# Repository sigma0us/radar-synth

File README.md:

# radar-synth
Dual PLL radar transmitter, design for prototyping

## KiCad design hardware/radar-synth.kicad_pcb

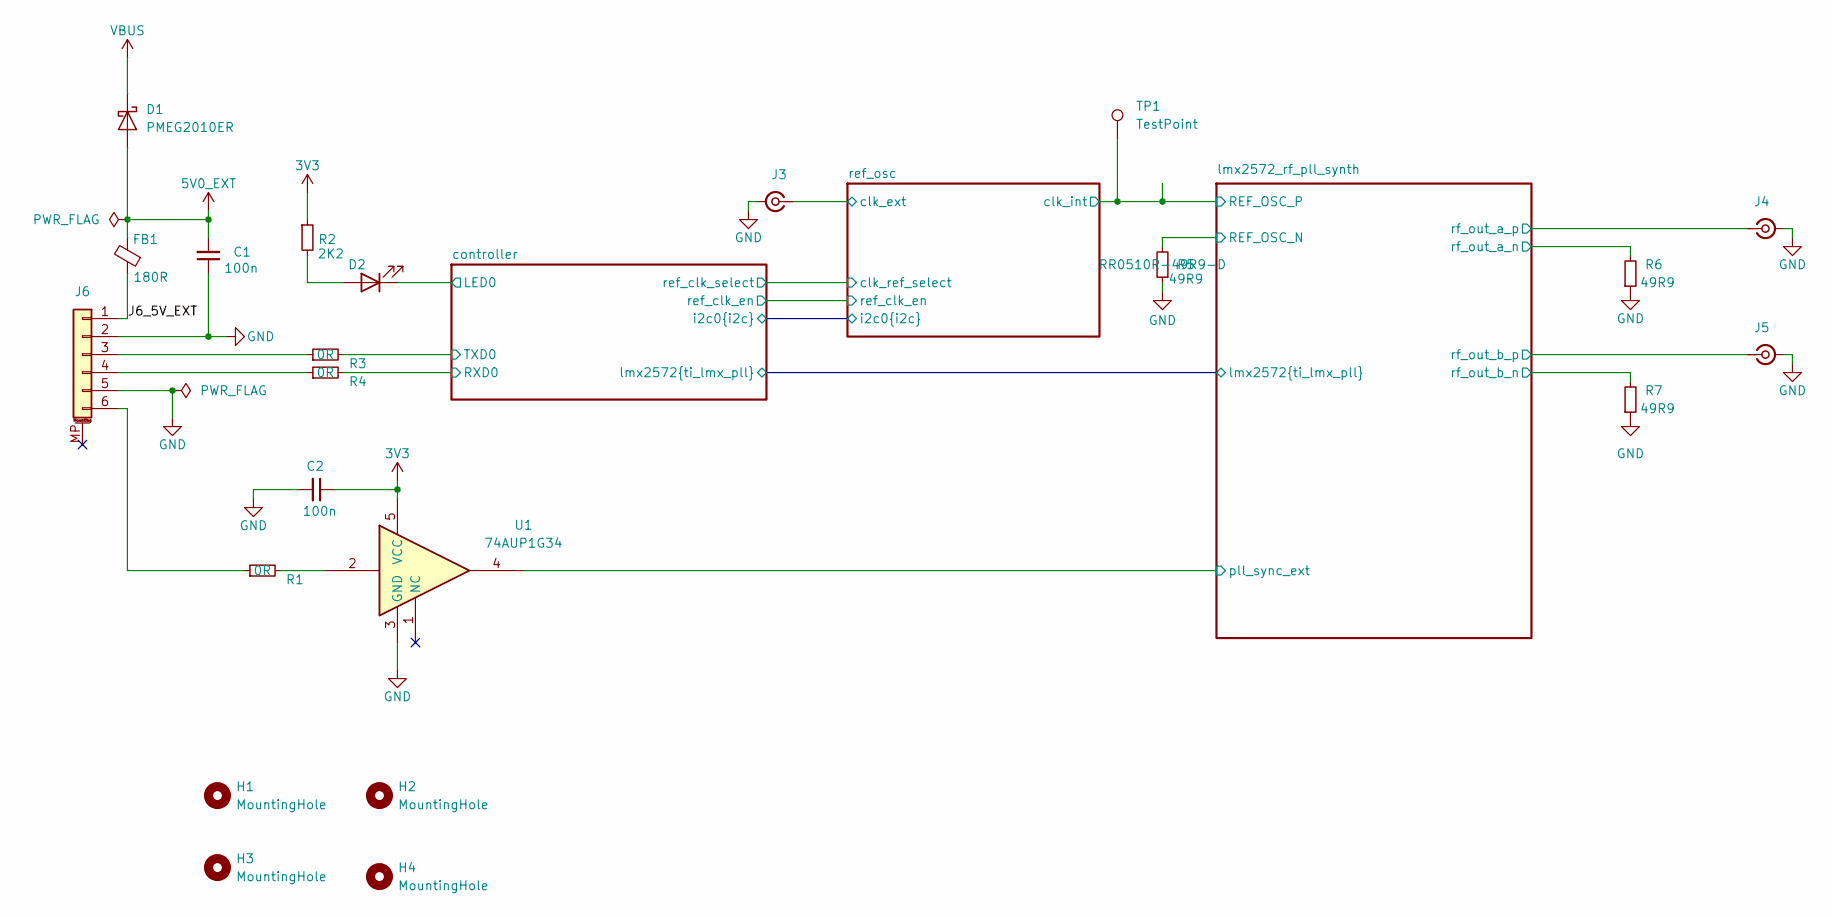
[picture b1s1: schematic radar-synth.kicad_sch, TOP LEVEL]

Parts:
C1, C2: 100n; C_0402_1005Metric; Voltage 25V; Tolerance 10%; MPN CL05B104KA5NNNC
D1: PMEG2010ER; Nexperia_CFP3_SOD-123W; MPN PMEG2010ER,115
D2: LED; LED_0603_1608Metric; MPN 150060SS75000
FB1: 180R; L_0402_1005Metric; MPN BLM15PX181SZ1D
H1, H2, H3, H4: MountingHole; MountingHole_2.7mm_M2.5
J3, J4, J5: Conn_Coaxial_Small; SMA_Samtec_SMA-J-P-H-ST-EM1_EdgeMount; MPN SMA-J-P-H-ST-EM1
J6: Conn_01x06_MountingPin; JST_GH_SM06B-GHS-TB_1x06-1MP_P1.25mm_Horizontal; MPN SM06B-GHS-TB
R1, R3, R4: 0R; R_0402_1005Metric; MPN ERJ-2GE0R00X
R2: 2K2; R_0402_1005Metric; MPN ERA-2AED222X
R5: 49R9; R_0402_1005Metric; Tolerance 5%; MPN RR0510R-49R9-D
R6, R7: 49R9; R_0402_1005Metric; MPN RR0510R-49R9-D
TP1: TestPoint; TestPoint_THTPad_1.0x1.0mm_Drill0.5mm
U1: 74AUP1G34; SOT-353_SC-70-5; MPN 74AUP1G34SE-7

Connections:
3V3: C2.1, R2.1, U1.5 (VCC); also elsewhere on the board
5V0_EXT: C1.2, D1.2 (A), FB1.2
/J6_5V_EXT: FB1.1, J6.1
/controller/LED0: D2.1 (K); also elsewhere on the board
/controller/RXD0: R4.2; also elsewhere on the board
/controller/TXD0: R3.2; also elsewhere on the board
/lmx2572_rf_pll_synth/REF_OSC_N: R5.2; also elsewhere on the board
/lmx2572_rf_pll_synth/REF_OSC_P: TP1.1; also elsewhere on the board
/lmx2572_rf_pll_synth/pll_sync_ext: U1.4; also elsewhere on the board
/lmx2572_rf_pll_synth/rf_out_a_n: R6.2; also elsewhere on the board
/lmx2572_rf_pll_synth/rf_out_a_p: J4.1 (In); also elsewhere on the board
/lmx2572_rf_pll_synth/rf_out_b_n: R7.2; also elsewhere on the board
/lmx2572_rf_pll_synth/rf_out_b_p: J5.1 (In); also elsewhere on the board
/ref_osc/clk_ext: J3.1 (In); also elsewhere on the board
GND: C1.1, C2.2, J3.2 (Ext), J4.2 (Ext), J5.2 (Ext), J6.2, J6.5, R5.1, R6.1, R7.1, U1.3 (GND); also elsewhere on the board
unnamed: D2.2 (A), R2.2
unnamed: J6.3, R3.1
unnamed: J6.4, R4.1
unnamed: J6.6, R1.1
unnamed: R1.2, U1.2
VBUS: D1.1 (K); also elsewhere on the board

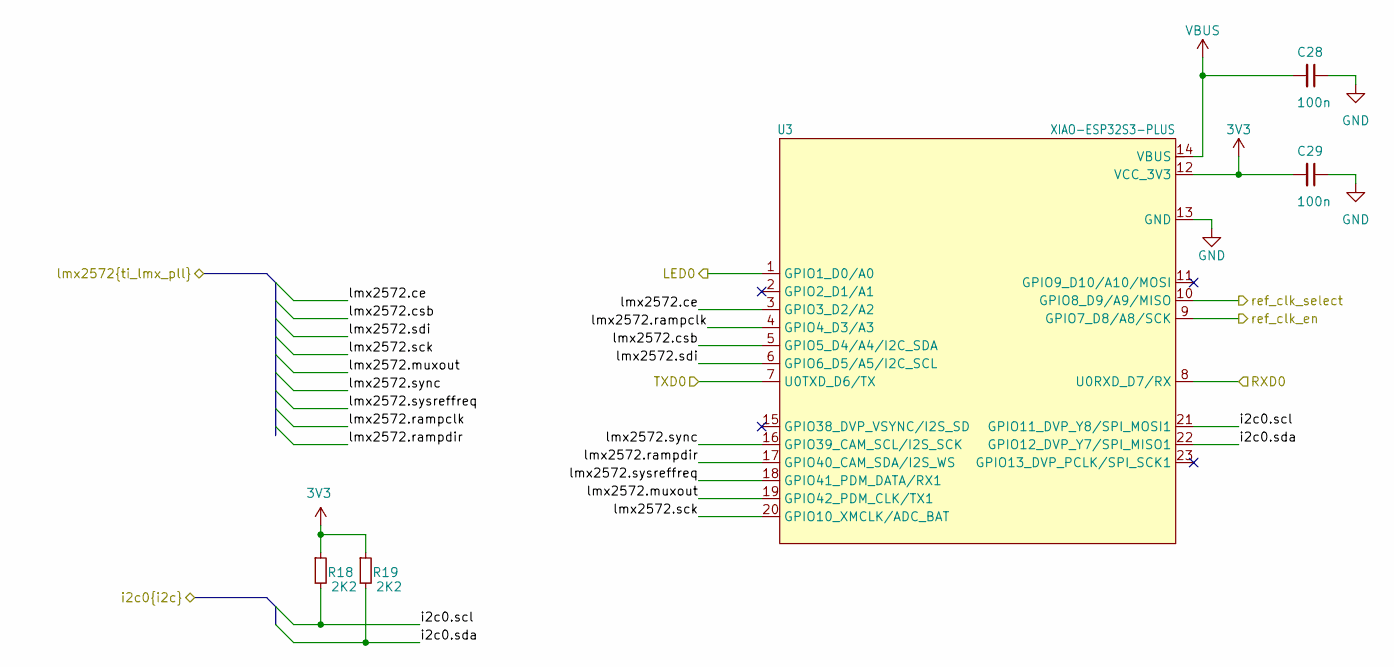
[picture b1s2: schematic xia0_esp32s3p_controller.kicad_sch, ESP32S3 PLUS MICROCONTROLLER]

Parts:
C28, C29: 100n; C_0402_1005Metric; Voltage 25V; Tolerance 10%; MPN CL05B104KA5NNNC
R18, R19: 2K2; R_0402_1005Metric; MPN ERA-2AED222X
U3: XIAO-ESP32S3-PLUS; XIAO-ESP32S3P-SMD-2.54-21X17.8MM; MPN 113991114

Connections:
3V3: C29.2, R18.1, R19.1, U3.12 (VCC_3V3); also elsewhere on the board
/controller/LED0: U3.1 (GPIO1_D0/A0); also elsewhere on the board
/controller/RXD0: U3.8 (U0RXD_D7/RX); also elsewhere on the board
/controller/TXD0: U3.7 (U0TXD_D6/TX); also elsewhere on the board
/controller/i2c0.scl: R18.2, U3.21 (GPIO11_DVP_Y8/SPI_MOSI1); also elsewhere on the board
/controller/i2c0.sda: R19.2, U3.22 (GPIO12_DVP_Y7/SPI_MISO1); also elsewhere on the board
/controller/lmx2572.ce: U3.3 (GPIO3_D2/A2); also elsewhere on the board
/controller/lmx2572.csb: U3.5 (GPIO5_D4/A4/I2C_SDA); also elsewhere on the board
/controller/lmx2572.muxout: U3.19 (GPIO42_PDM_CLK/TX1); also elsewhere on the board
/controller/lmx2572.rampclk: U3.4 (GPIO4_D3/A3); also elsewhere on the board
/controller/lmx2572.rampdir: U3.17 (GPIO40_CAM_SDA/I2S_WS); also elsewhere on the board
/controller/lmx2572.sck: U3.20 (GPIO10_XMCLK/ADC_BAT); also elsewhere on the board
/controller/lmx2572.sdi: U3.6 (GPIO6_D5/A5/I2C_SCL); also elsewhere on the board
/controller/lmx2572.sync: U3.16 (GPIO39_CAM_SCL/I2S_SCK); also elsewhere on the board
/controller/lmx2572.sysreffreq: U3.18 (GPIO41_PDM_DATA/RX1); also elsewhere on the board
/controller/ref_clk_en: U3.9 (GPIO7_D8/A8/SCK); also elsewhere on the board
/controller/ref_clk_select: U3.10 (GPIO8_D9/A9/MISO); also elsewhere on the board
GND: C28.1, C29.1, U3.13 (GND); also elsewhere on the board
VBUS: C28.2, U3.14 (VBUS); also elsewhere on the board

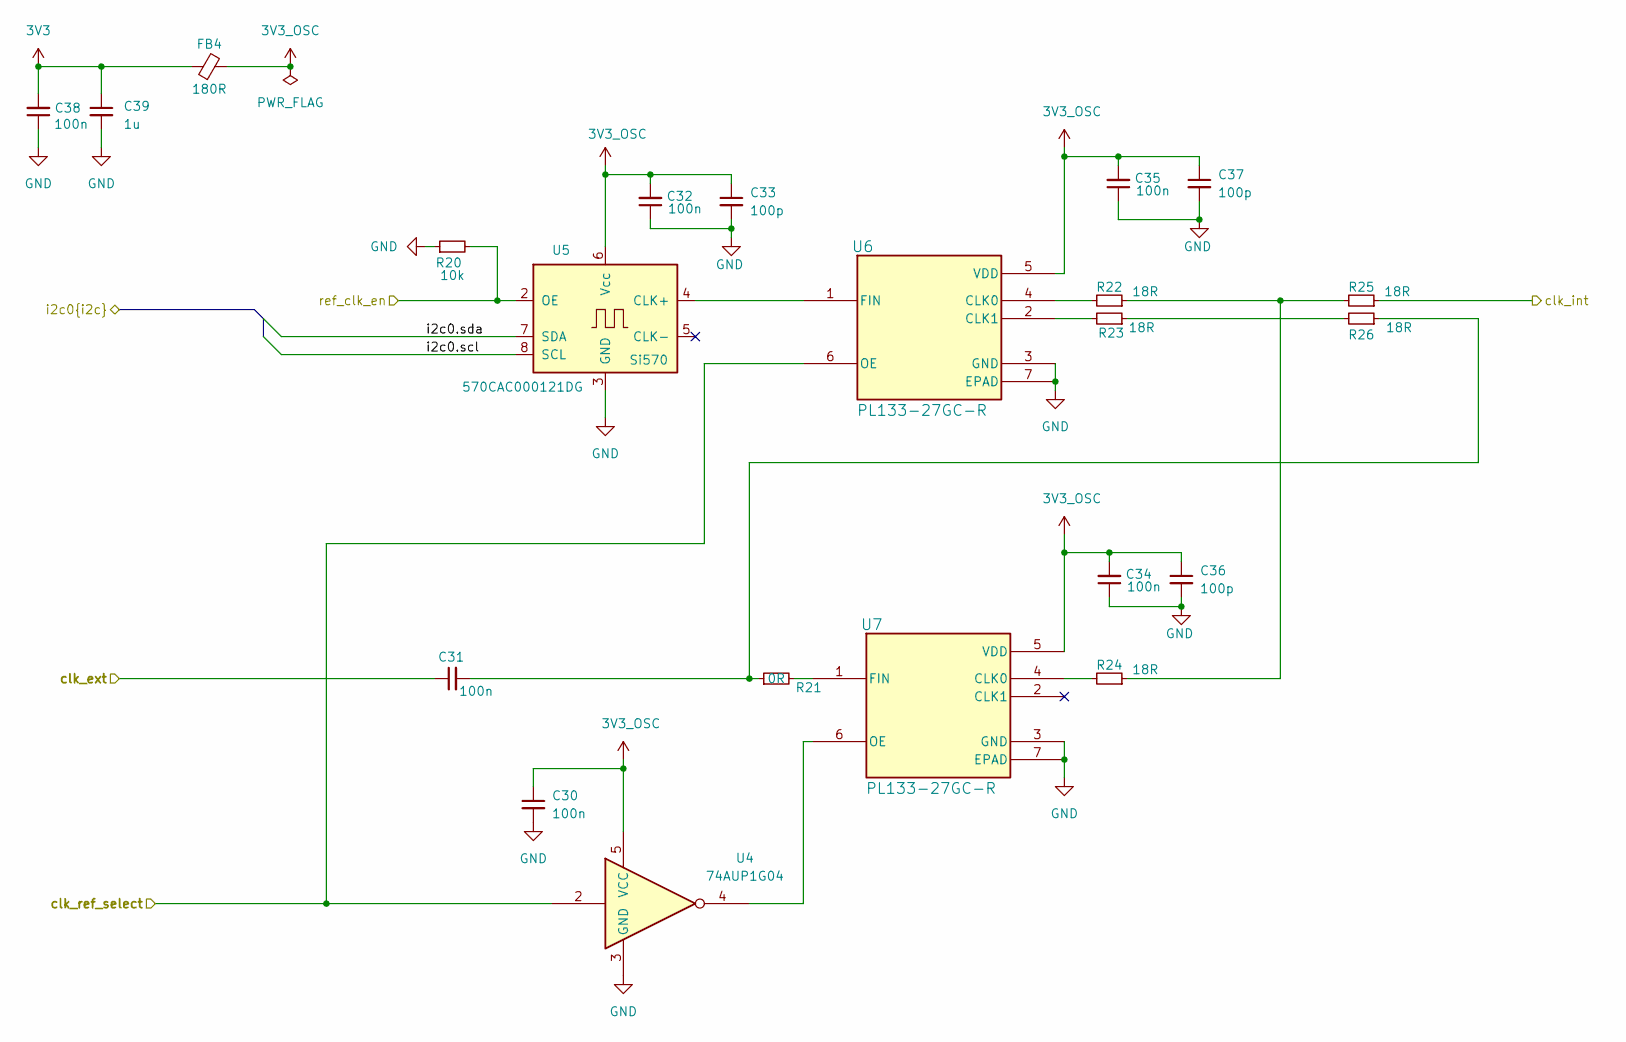
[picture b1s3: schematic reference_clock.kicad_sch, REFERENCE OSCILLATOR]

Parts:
C30: 100n; C_0402_1005Metric; MPN CL05B104KA5NNNC
C31, C32, C34, C35, C38: 100n; C_0402_1005Metric; Voltage 25V; Tolerance 10%; MPN CL05B104KA5NNNC
C33, C36, C37: 100p; C_0402_1005Metric; MPN KGM05AR71H101KN
C39: 1u; C_0402_1005Metric; Voltage 16V; Tolerance 10%; MPN EMK105BJ105KV-F
FB4: 180R; L_0402_1005Metric; MPN BLM15PX181SZ1D
R20: 10k; R_0402_1005Metric; MPN RC0402JR-0710KL
R21: 0R; R_0402_1005Metric; MPN ERJ-2GE0R00X
R22, R23, R24, R25, R26: 18R; R_0402_1005Metric; MPN CR0402-FX-18R0GLF
U4: 74AUP1G04; SOT-353_SC-70-5; MPN SN74AUP1G04DCKR
U5: Si570; Oscillator_SMD_SI570_SI571_Standard; MPN 570CAC000121DG
U6, U7: PL133-27GC-R; TDFN2013-6LD-PL-1_MCH; MPN PL133-27GC-R

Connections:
3V3: C38.2, C39.1, FB4.1; also elsewhere on the board
3V3_OSC: C30.1, C32.2, C33.1, C34.2, C35.2, C36.1, C37.1, FB4.2, U4.5 (VCC), U5.6 (Vcc), U6.5 (VDD), U7.5 (VDD)
/controller/i2c0.scl: U5.8 (SCL); also elsewhere on the board
/controller/i2c0.sda: U5.7 (SDA); also elsewhere on the board
/controller/ref_clk_en: R20.2, U5.2 (OE); also elsewhere on the board
/controller/ref_clk_select: U4.2, U6.6 (OE); also elsewhere on the board
/lmx2572_rf_pll_synth/REF_OSC_P: R25.1; also elsewhere on the board
/ref_osc/clk_ext: C31.1; also elsewhere on the board
GND: C30.2, C32.1, C33.2, C34.1, C35.1, C36.2, C37.2, C38.1, C39.2, R20.1, U4.3 (GND), U5.3 (GND), U6.3 (GND), U6.7 (EPAD), U7.3 (GND), U7.7 (EPAD); also elsewhere on the board
unnamed: C31.2, R21.1, R26.1
unnamed: R22.1, R24.1, R25.2
unnamed: R23.1, R26.2
unnamed: U5.4 (CLK+), U6.1 (FIN)
unnamed: R22.2, U6.4 (CLK0)
unnamed: R23.2, U6.2 (CLK1)
unnamed: R24.2, U7.4 (CLK0)
unnamed: R21.2, U7.1 (FIN)
unnamed: U4.4, U7.6 (OE)

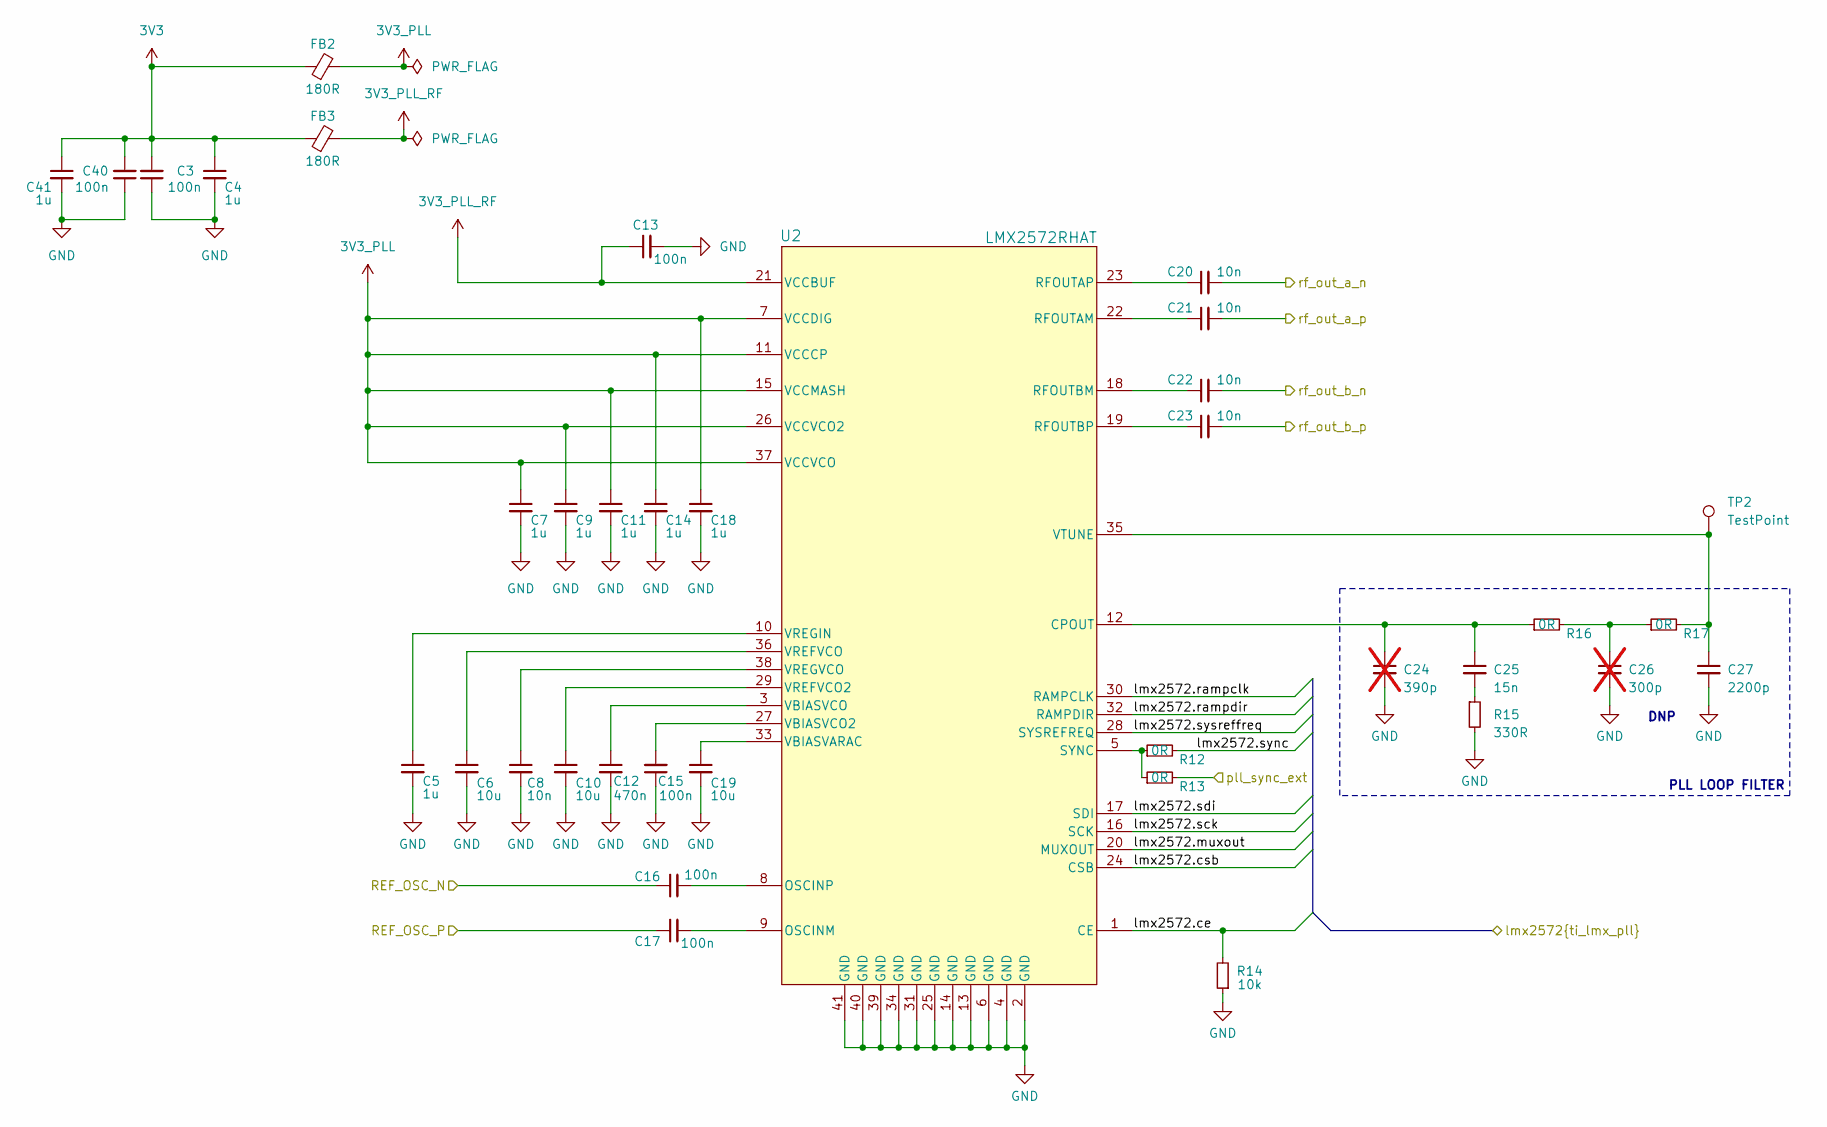
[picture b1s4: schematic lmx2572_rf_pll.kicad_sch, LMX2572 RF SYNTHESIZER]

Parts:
C3, C13, C15, C16, C17, C40: 100n; C_0402_1005Metric; Voltage 25V; Tolerance 10%; MPN CL05B104KA5NNNC
C4, C5, C7, C9, C11, C14, C18, C41: 1u; C_0402_1005Metric; Voltage 16V; Tolerance 10%; MPN EMK105BJ105KV-F
C6, C10, C19: 10u; C_0402_1005Metric; Voltage 10v; Tolerance 20%; MPN GRM155R61A106ME11D
C8, C20, C21, C22, C23: 10n; C_0402_1005Metric; Voltage 16V; Tolerance 10%; MPN 520L103KT16T
C12: 470n; C_0603_1608Metric; Voltage 25V; Tolerance 10%; MPN MBAST168SB7474KTNA18
C24: 390p; C_0402_1005Metric; MPN GRM1555C1H391JA01D; not fitted
C25: 15n; C_0402_1005Metric; MPN C0402C153J4RACTU
C26: 300p; C_0402_1005Metric; MPN GRM1555C1H301JA01D; not fitted
C27: 2200p; C_0402_1005Metric; MPN VJ0402Y222JXXAC
FB2, FB3: 180R; L_0402_1005Metric; MPN BLM15PX181SZ1D
R12, R13, R16, R17: 0R; R_0402_1005Metric; MPN ERJ-2GE0R00X
R14: 10k; R_0402_1005Metric; MPN RC0402JR-0710KL
R15: 330R; R_0402_1005Metric; MPN RC0402JR-07330RL
TP2: TestPoint; TestPoint_THTPad_1.0x1.0mm_Drill0.5mm
U2: LMX2572RHAT; RHA0040H; MPN LMX2572RHAT

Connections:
3V3: C3.2, C4.1, C40.2, C41.1, FB2.1, FB3.1; also elsewhere on the board
3V3_PLL: C7.1, C9.1, C11.1, C14.1, C18.1, FB2.2, U2.7 (VCCDIG), U2.11 (VCCCP), U2.15 (VCCMASH), U2.26 (VCCVCO2), U2.37 (VCCVCO)
3V3_PLL_RF: C13.1, FB3.2, U2.21 (VCCBUF)
/controller/lmx2572.ce: R14.2, U2.1 (CE); also elsewhere on the board
/controller/lmx2572.csb: U2.24 (CSB); also elsewhere on the board
/controller/lmx2572.muxout: U2.20 (MUXOUT); also elsewhere on the board
/controller/lmx2572.rampclk: U2.30 (RAMPCLK); also elsewhere on the board
/controller/lmx2572.rampdir: U2.32 (RAMPDIR); also elsewhere on the board
/controller/lmx2572.sck: U2.16 (SCK); also elsewhere on the board
/controller/lmx2572.sdi: U2.17 (SDI); also elsewhere on the board
/controller/lmx2572.sync: R12.2; also elsewhere on the board
/controller/lmx2572.sysreffreq: U2.28 (SYSREFREQ); also elsewhere on the board
/lmx2572_rf_pll_synth/REF_OSC_N: C16.1; also elsewhere on the board
/lmx2572_rf_pll_synth/REF_OSC_P: C17.1; also elsewhere on the board
/lmx2572_rf_pll_synth/pll_sync_ext: R13.2; also elsewhere on the board
/lmx2572_rf_pll_synth/rf_out_a_n: C20.2; also elsewhere on the board
/lmx2572_rf_pll_synth/rf_out_a_p: C21.2; also elsewhere on the board
/lmx2572_rf_pll_synth/rf_out_b_n: C22.2; also elsewhere on the board
/lmx2572_rf_pll_synth/rf_out_b_p: C23.2; also elsewhere on the board
GND: C3.1, C4.2, C5.2, C6.2, C7.2, C8.2, C9.2, C10.2, C11.2, C12.2, C13.2, C14.2, C15.1, C18.2, C19.2, C24.2, C26.2, C27.2, C40.1, C41.2, R14.1, R15.2, U2.2 (GND), U2.4 (GND), U2.6 (GND), U2.13 (GND), U2.14 (GND), U2.25 (GND), U2.31 (GND), U2.34 (GND), U2.39 (GND), U2.40 (GND), U2.41 (GND), U2.V; also elsewhere on the board
unnamed: C25.2, R15.1
unnamed: C26.1, R16.2, R17.1
unnamed: C24.1, C25.1, R16.1, U2.12 (CPOUT)
unnamed: C17.2, U2.9 (OSCINM)
unnamed: C16.2, U2.8 (OSCINP)
unnamed: C21.1, U2.22 (RFOUTAM)
unnamed: C20.1, U2.23 (RFOUTAP)
unnamed: C22.1, U2.18 (RFOUTBM)
unnamed: C23.1, U2.19 (RFOUTBP)
unnamed: R12.1, R13.1, U2.5 (SYNC)
unnamed: C19.1, U2.33 (VBIASVARAC)
unnamed: C15.2, U2.27 (VBIASVCO2)
unnamed: C12.1, U2.3 (VBIASVCO)
unnamed: C10.1, U2.29 (VREFVCO2)
unnamed: C6.1, U2.36 (VREFVCO)
unnamed: C5.1, U2.10 (VREGIN)
unnamed: C8.1, U2.38 (VREGVCO)
unnamed: C27.1, R17.2, TP2.1, U2.35 (VTUNE)

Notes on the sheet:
DNP
PLL LOOP FILTER

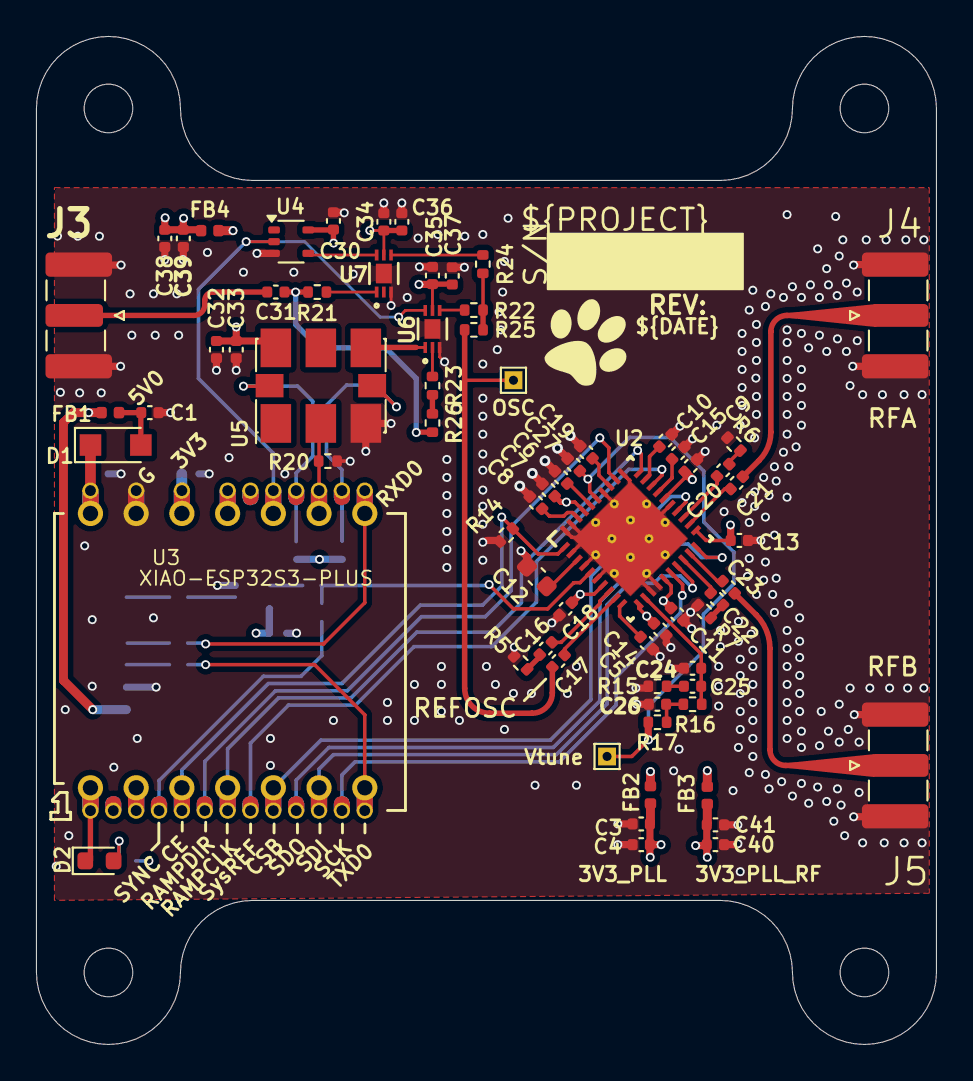
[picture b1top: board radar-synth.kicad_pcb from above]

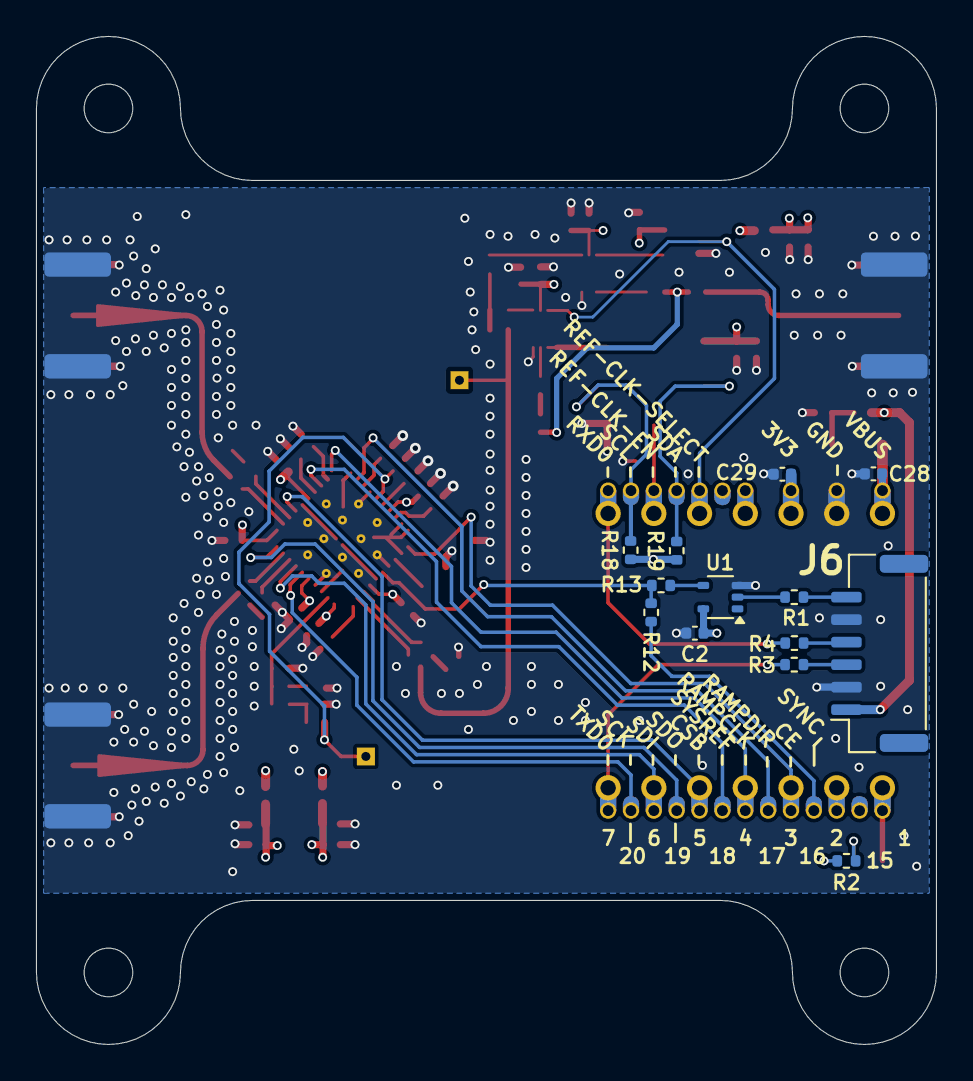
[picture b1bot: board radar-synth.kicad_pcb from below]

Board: 4 copper layers, 50.0 x 56.0 mm, 86 parts (13 on the bottom side), 64 nets.

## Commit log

2024-12-30 Initial release
2025-03-28 Completed schematics
2025-03-30 Completed core PCB routing
2025-03-30 Ready for FAB info
2025-03-31 Sent off for quote
2025-03-31 Fixed silkscreen and re-submitted
2025-05-26 Updated firmware
